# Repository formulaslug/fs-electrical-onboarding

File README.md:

# FS Electrical Onboarding

This git repository contains onboarding projects for each electrical subsystem:

- Low Voltage (LV)
- Power Electronics (PE)
- Firmware (FW)

You must complete one onboarding project to be able to join the team. Our goal
is to get to know you and how you work, not to grade your skills or abilities
coming in. We want to see that you're excited and willing to learn, not that you
know everything already! To make team roster selection easier for us, you'll
only officially be assigned to one specific subsystem within the Electrical
team. But once you've joined, you're encouraged to contribute and participate in
as many ways as you're excited to and have bandwidth for.

**Read the README file in each subsystem's folder in this repo to get started on
the onboarding project for that subsystem.** You are encouraged to attempt
whichever of the three onboarding projects that you find interesting!

---

Note: Clone this repository recursively (`git clone --recursive`). If you
didn't, be sure to initialize the submodule: `git submodule init` _and_ `git
submodule update`

**IMPORTANT:** To start your project, create a branch in this repo with your
first and last name. For example: `jack-nystrom`. Then do your work in that
branch!

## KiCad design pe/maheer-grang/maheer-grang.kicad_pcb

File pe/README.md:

**Formula Slug Power Electronics Onboarding**

Welcome to Formula Slug's Power Eletronics onboarding project! Refer to this
Google Doc for all information regarding this project:

[View the FS Power Electronics Onboarding Guide 26-27](https://docs.google.com/document/d/1htf_bj8dCnWR_2gC1TFTzJU0MFP1d0OxF1IBO_kqalM/edit?usp=sharing)

---

Note: Clone this repository recursively (`git clone --recursive`). If you
didn't, be sure to initialize the submodule: `git submodule init` _and_ `git
submodule update`

**IMPORTANT:** To start your project, create a branch in this repo with your
first and last name. For example: `jack-nystrom`. Then do your work in that
branch!

# Kicad Projects

## Creating a project

1. Install our Template Project to your local computer.
   - Kicad requires templates to be installed locally, but our template is
     stored in the `template` folder in this repo, so you'll need to copy the
     `template` folder to where Kicad expects it. To see where that is, press
     Preferences -> Configure Paths, and look for the value of
     `KICAD_USER_TEMPLATE_DIR`. Copy the `template` folder there.
2. Create a new branch _from main_. Name your branch in-kebab-case
3. Create a new Kicad project from template. Under "User Templates" you should
   now see our Formula Slug template listed! Navigate to `fs-5-schematics` in
   the dialog and name your project the same as your branch name
   (in-kebab-case). This should create a new folder for your project inside of
   `fs-5-schematics`.
5. In the Schematic Editor, open File -> Schematic Setup -> Text Variables, and
   fill in the info for your board.
6. Create an initial commit and get to work!

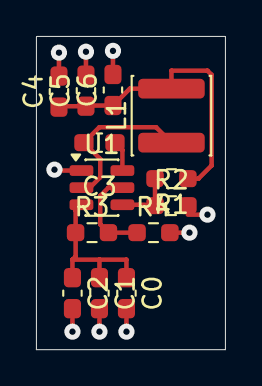
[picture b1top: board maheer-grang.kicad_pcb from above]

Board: 2 copper layers, 10.5 x 17.4 mm, 13 parts (0 on the bottom side), 7 nets.

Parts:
C0, C1, C2: 10 µF; C_0603_1608Metric_Pad1.08x0.95mm_HandSolder
C3: 100 nF; C_0603_1608Metric_Pad1.08x0.95mm_HandSolder
C4, C5, C6: 22 µF; C_0603_1608Metric_Pad1.08x0.95mm_HandSolder
L1: 4.7 µH; L_Pulse_PA4332
R1: 56.2k; R_0603_1608Metric_Pad0.98x0.95mm_HandSolder
R2: 10K; R_0603_1608Metric_Pad0.98x0.95mm_HandSolder
R3: 221K; R_0603_1608Metric_Pad0.98x0.95mm_HandSolder
R4: 32.4K; R_0603_1608Metric_Pad0.98x0.95mm_HandSolder
U1: AP62300TWU; TSOT-23-6

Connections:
GNDREF: C0.2, C1.2, C2.2, C4.2, C5.2, C6.2, R2.2, R4.2, U1.1 (GND)
unnamed: C4.1, C5.1, C6.1, L1.2, R1.1
unnamed: C3.1, U1.6 (BST)
unnamed: R3.2, R4.1, U1.5 (EN)
unnamed: R1.2, R2.1, U1.4 (FB)
unnamed: C0.1, C1.1, C2.1, R3.1, U1.3 (IN)
unnamed: C3.2, L1.1, U1.2 (SW)

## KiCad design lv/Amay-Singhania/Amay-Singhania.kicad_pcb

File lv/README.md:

**Welcome to Formula Slug Low Voltage Onboarding**

In order to get to know you and your passions better, we are asking you to complete
an open ended racecar-related project in one of a few formats. Our goal is not
to evaluate any of your skills, but rather to learn about how you approach difficult
and uncertian things.

For the purposes of whichever LV project you choose to do, **I (Luca) am available to help you!**
(and would appreciate getting to know you better)
I will be in BE-49 (or sometimes Jacks Lounge) at the times published in the electrical leads
office hours calendar, and you can always shoot me a slack message.

# What does LV do?
LV team designs all the PCBs and electrical wiring on the car. There's lots of
interesting safety features which are rules required to be implemented in hardware,
and we also try to pack more and more sensors onto the car each year.

As part of LV, you should expect to face challenges like:
- Design a circuit to detect a high-current output from the battery at the same time
as high brake pressure (see: BSPD)
- Design a circuit to measure small resistance changes of a circuit in a high-noise
enviornment (see: Strain Gauges)
- Select parts (sheathing, wire, crimps) with which to wire the car
- Debug startup transient conditions causing fault lights to flash when the car
is turned on
- Layout components on a PCB to obey mechanical, thermal, and safety constraints
- Source and implement sensors
- Debug communication busses on the car like CAN, analog signals, Serial, an PWM

You can find exmaples of the work LV has done all over the car, as well as in
the [schematics repository](https://github.com/formulaslug/fs-4-schematics). You
can also see some awesome sensor data collected on LV PCBs in our [grafana
dashboard](https://graf.telemetry.formulaslug.com/d/lyffkrd/library-dashboard?orgId=1&from=1970-01-01T00:00:00.011Z&to=1970-01-01T00:04:08.856Z&timezone=utc&var-srcfile=FS-4%2Fttt%2Fcandump-2026-06-11_155420.parquet).

# Project Options
Reminder: These are big bites, we know that most poeple can't produce a car-ready
outcome for any of these... that's okay :). We just want to see how you'll go at
it. Aim to spend less than 5 hours on these, and try to involve as much of your
own thinking as possible. Your personal effort will be noticed. Chose one of these
projects, create a branch of this repository, and create a subfolder of /lv containing
your work/research. You can also propose literally anything else you'd like to do
as an onboarding project.

> [!CAUTION]
> **Don't get overwhelmed. Come talk to me. I want to help you. This is supposed to be hard. You're not supposed to do a good job.**

## Air pressure / temperature / humidity
Our racecar has two main applications for aerometric sensors: monitoring the
cooling of the battery, and validating simulations of the aerodynamic elements
on the car. Do some research to determine what parameters (accuracy, resolution,
range) are needed for these applications and source a sensor (on digikey or mouser).
You can also describe how you'd make your own sensor (or sensor array) for this applciation
(and I'd love to hear it).

One example of such a sensor is the [BMP180](https://www.digikey.com/en/products/detail/bosch-sensortec/BMP180/2688259).
It's a MEMS (micro electro mechanical system) which measures pressure. It has great software
support because lots of Arduino modules use it, but it's no longer manufactured, and has
decent resolution, but since it communicates with I2C and has no address pins (inputs which allow I2C address configuration), it would be
difficult to use several of them together with one microcontroller.

Try to find a sensor which has at least the resolution of the BMP180, but has a communication
or output interface which allows it to be banked with several others on the same PCB. I
recommend reading briefly about common sensor output interfaces (analog, I2C, SPI, oneWire),
so you can understand which are easiest to use with multiple of the same sensor.

Identify some key parameters, and compile your questions/thoughts, and then **check in with me.**

## FPC suspension strain gauge
We order our PCBs from [JLC](https://jlcpcb.com). JLC can also make something called
an [FPC](https://jlcpcb.com/pcb-fabrication/flexible-pcb). Read about how [strain gauges](https://en.wikipedia.org/wiki/Strain_gauge) 
work, do some research about how other FSAE teams have
implemented strain gauges on their suspension members, and attempt to design your own
strain gauge to be manufactured as an FPC. I have not seen other teams do this before, but
it has some benefits and drawbacks... try to find those. 

Once you've put some thought into it and have an idea of how these things work, I want you to
do a teeny bit of math. Use an online calculator, relevant equations and constants, or the
calculator built into Kicad to compute the necessary length of minimum width copper trace ([here are jlc's minimums](https://jlcpcb.com/capabilities/flex-pcb-capabilities))
needed to equal 350 Ohm's of resistance. Take this a step farther, and determine the size of
rectangle needed to fit those traces according to JLC's published minimum trace width and
trace clearance (width between traces).

At this point or if you get stuck, **come check in with me.**

This project will be a PCB, so
instead of creating a blank folder with markdown or text files documenting your research,
create a copy of the kicad template folder (see below). You can still include any research
as text files. This is one project we are very excited about as a team, and which will make
a big impact on DAQ (Data Aquisition).

## Design a BSPD circuit
Every FSAE EV car is required to have a device called the "Brake system plausibility device".
Read about it in EV8.7 of the [2027 rules](https://fsaeonline.com/cdsweb/gen/DownloadDocument.aspx?DocumentID=9574fa97-c13e-4b90-9c75-044e30348cab).
We use the following sensors for this device, but you can choose others for the purpose of this project if you prefer:
- [Brake Pressure](https://www.summitracing.com/parts/aag-s0050?srsltid=AU7gw4WvwmFzL4ESdIDoUFAQyi38mjfxpO6NWv7JNG3hZhB_v7D9QLCm)
- [Current Sensor](https://www.lem.com/sites/default/files/products_datasheets/hass-50_600-s-v22.pdf)
This project will be a schematic, so instead of creating a blank folder with markdown or 
text files documenting your research, create a copy of the kicad template folder 
(see below). You can still include any research as text files.

Hint: You'll need to use Op-Amps to compare and scale voltages.

You do not need to start immediately with Kicad. It can be a bit much. Start by creating a
schematic for an Op-Amp based comparator (google that). Capture it somehow (on paper, in Kicad, whatever).
**Then come and check in with me to talk it through.**

I expect many of you will be overwhelmed trying to figure out how op-amps work. Find some resources (a video, article, etc),
and as you hear terms you do not understand, work your way backwards. You can learn much of the fundamentals of
~2 entire classes if you are intellectually responsible in teaching yourself this way. If you feel like giving up, come
find me.

## In-Helmet Audio
We want to add radio based driver communications to our telemetry system. This project
specifically relates to the speakers and microphone in the drivers (motorcycle) helmet,
and perhaps the driver circuitry to convert a convenient digital signal to and from the
interface to the microphone/speakers. Find speakers and microphone(s) sourceable on
digikey and propose how they can be packaged into the helmet without compromising ergonomics.
Think about how this system can connect to wiring on the car with a connector
that is both robust and breakaway--that is, the driver needs to be able to get out of the car
quickly in an emergency and won't have time to unlatch any extra electrical connections.

[Here's](https://www.digikey.com/en/products/detail/same-sky-formerly-cui-devices/CSS-66668N/6145945) 
an example of the type of speaker driver that would be in a pair of headphones.
This particular one is very large. Determine if a large driver is necessary in this application,
or rather what advantage a larger driver has, and find one which is appropriate. Similarly,
think about the challenges a microphone in this application faces, and try to find one which
is suitable.

As you select components, remember to focus on both their electrical/audio performance,
and their ergonomics/dimensions as they relate to this application. **Find me when you source
at least 2/3 components (microphone, speaker, connector).**

# General Notes

- Clone this repository recursively (`git clone --recursive`). If you didn't, be
  sure to initialize the submodule: `git submodule init` _and_ `git submodule
update`

**IMPORTANT:** To start your project, create a branch in this repo with your
first and last name. For example: `jack-nystrom`. Then do your work in that
branch!

# Kicad Projects

## Creating a project

1. Install our Template Project to your local computer.
   - Kicad requires templates to be installed locally, but our template is
     stored in the `template` folder in this repo, so you'll need to copy the
     `template` folder to where Kicad expects it. To see where that is, press
     Preferences -> Configure Paths, and look for the value of
     `KICAD_USER_TEMPLATE_DIR`. Copy the `template` folder there.
2. Create a new branch _from main_. Name your branch in-kebab-case
3. Create a new Kicad project from template. Under "User Templates" you should
   now see our Formula Slug template listed! Navigate to `fs-5-schematics` in
   the dialog and name your project the same as your branch name
   (in-kebab-case). This should create a new folder for your project inside of
   `fs-5-schematics`.
5. In the Schematic Editor, open File -> Schematic Setup -> Text Variables, and
   fill in the info for your board.
6. Create an initial commit and get to work!

## LV Standards

https://docs.google.com/document/d/1JF8Ld86JzdSsicxHTWAqBsUBFZuK-cVn7AItZKhkslQ/edit?usp=sharing

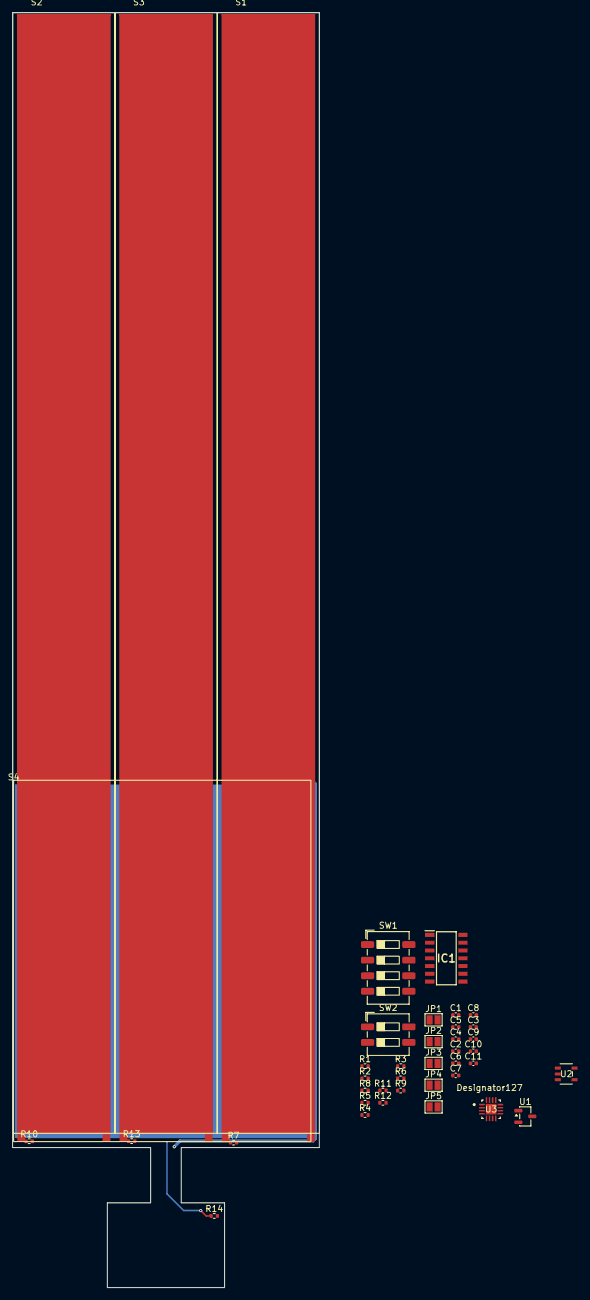
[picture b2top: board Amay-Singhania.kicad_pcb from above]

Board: 2 copper layers, 50.0 x 207.8 mm, 40 parts (0 on the bottom side), 25 nets.

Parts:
C1, C2, C3, C5, C6, C7, C8: 0.1uF; C_0402_1005Metric
C4: 100uF; C_0402_1005Metric
C9, C10, C11: 100nF; C_0402_1005Metric
IC1: TLV4888DR; SOIC127P600X175-14N
JP1, JP2, JP3, JP4, JP5: SolderJumper-2_P1.3mm_Open_Pad1.0x1.5mm
R1, R2, R7, R10, R13, R14: 350; R_0402_1005Metric
R3, R4, R8, R11, R12: 470R; R_0402_1005Metric
R5: 10kR; R_0402_1005Metric
R6, R9: 4.7kR; R_0402_1005Metric
S1, S2, S3: StrainGaugeAxial; Strain Gauge V1
S4: StrainGaugeReference; ReferenceStrainGauge
SW1: SW_DIP_x04; SW_DIP_SPSTx04_Slide_6.7x11.72mm_W6.73mm_P2.54mm_LowProfile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
SW2: SW_DIP_x02; SW_DIP_SPSTx02_Slide_6.7x6.64mm_W6.73mm_P2.54mm_LowProfile_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
U1: SL7550-3; SOT-23-3
U2: LDK320AM33R; SOT23-5L_STM
U3: ADS122C14IRTER; RTE0016C-IPC_A

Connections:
1V65: C3.2, JP5.2, R3.1, U3.8 (AIN7_GPIO3_DRDY_CLKIN_N)
+3V3: C9.1, C10.1, R1.1, R6.1, R9.1, S1.2, S2.2, S3.2, S4.2, SW1.5, SW2.3, U2.5 (OUT), U3.13 (DVDD), U3.15 (AVDD)
+5V: C1.1, IC1.4 (V+), U1.2 (VOUT), U2.1 (IN), U2.3 (EN)
ADC_SCL: R6.2, SW1.7, U3.12 (SCL)
ADC_SDA: R9.2, SW1.8, U3.11 (SDA)
Center_Gauge: C2.2, JP1.1, R4.2, U3.3 (AIN2)
Center_Gauge_Unbuffered: IC1.5 (+IN_B), R7.1, S1.1
GND: C1.2, C2.1, C3.1, C4.1, C5.1, C6.1, C7.1, C8.2, C9.2, C10.2, C11.1, R2.2, R7.2, R10.2, R13.2, R14.2, SW1.6, SW2.4, U1.1 (GND), U2.2 (GND), U3.14 (GND), U3.17 (Thermal_Pad)
Left_Gauge: C7.2, JP3.1, R12.2, U3.1 (AIN0)
Left_Gauge_Unbuffered: IC1.12 (+IN_D), R10.1, S2.1
unnamed: IC1.1 (OUT_A), IC1.2 (-IN_A), R5.2, R8.2
unnamed: IC1.6 (-IN_B), IC1.7 (OUT_B), JP1.2, R4.1
unnamed: IC1.8 (OUT_C), IC1.9 (-IN_C), JP2.2, R11.1
unnamed: IC1.13 (-IN_D), IC1.14 (OUT_D), JP3.2, R12.1
unnamed: C8.1, IC1.11 (V-)
unnamed: R1.2, R2.1, R3.2
unnamed: SW1.1, SW1.2, SW1.3, SW1.4, U3.9 (A0)
unnamed: SW2.1, SW2.2, U3.10 (A1)
unnamed: JP4.2, JP5.1, U3.2 (AIN1), U3.4 (AIN3), U3.6 (AIN5_REFN_GPIO1)
unnamed: C11.2, U3.16 (REFOUT)
Reference_Gauge: C5.2, R8.1, U3.7 (AIN6_GPIO2_FAULT_N)
Reference_Gauge_Filtered: C4.2, JP4.1, R5.1
Reference_Gauge_Unbuffered: IC1.3 (+IN_A), R14.1, S4.1
Right_Gauge: C6.2, JP2.1, R11.2, U3.5 (AIN4_REFP_GPIO0)
Right_Gauge_Unbuffered: IC1.10 (+IN_C), R13.1, S3.1

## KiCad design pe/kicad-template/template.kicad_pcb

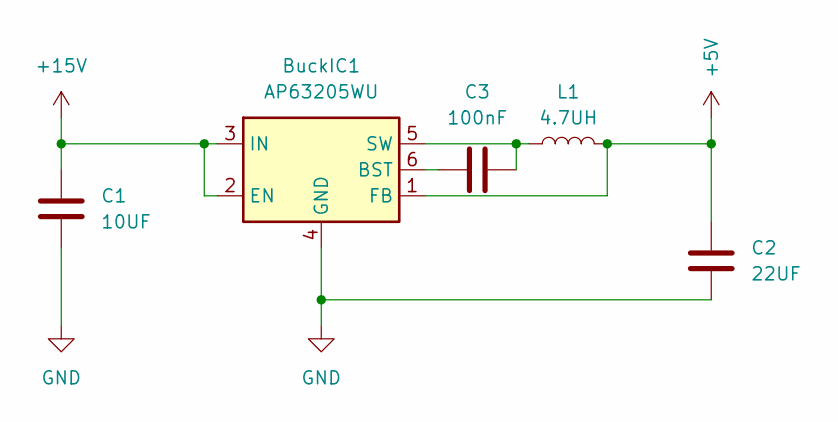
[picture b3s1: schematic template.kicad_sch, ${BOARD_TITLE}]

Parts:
BuckIC1: AP63205WU; TSOT-23-6; MFG PN AP63205WU-7; DIGI PN AP63205WU-7DITR-ND
C1: 10UF; C_0603_1608Metric; MFG PN CC0603MRX5R8BB106; Digi PN 311-3494-2-ND
C2: 22UF; C_0603_1608Metric; MFG PN C1608X5R1A226M080DC; DIGI PN 445-C1608X5R1A226M080DCTR-ND
C3: 100nF; C_0603_1608Metric; MFG PN C0603C104K5RACTU; DIGI PN 399-C0603C104K5RACTUTR-ND
L1: 4.7UH; L_Bourns_SRP5030T; MFG PN SRP5030TA-4R7M; DIGI PN SRP5030TA-4R7MTR-ND

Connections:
+5V: BuckIC1.1 (FB), C2.1, L1.2
+15V: BuckIC1.2 (EN), BuckIC1.3 (IN), C1.1
GND: BuckIC1.4 (GND), C1.2, C2.2
unnamed: BuckIC1.6 (BST), C3.1
unnamed: BuckIC1.5 (SW), C3.2, L1.1

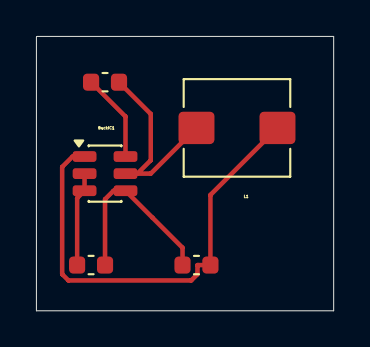
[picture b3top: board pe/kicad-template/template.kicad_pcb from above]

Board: 2 copper layers, 16.5 x 15.2 mm, 5 parts (0 on the bottom side), 5 nets.

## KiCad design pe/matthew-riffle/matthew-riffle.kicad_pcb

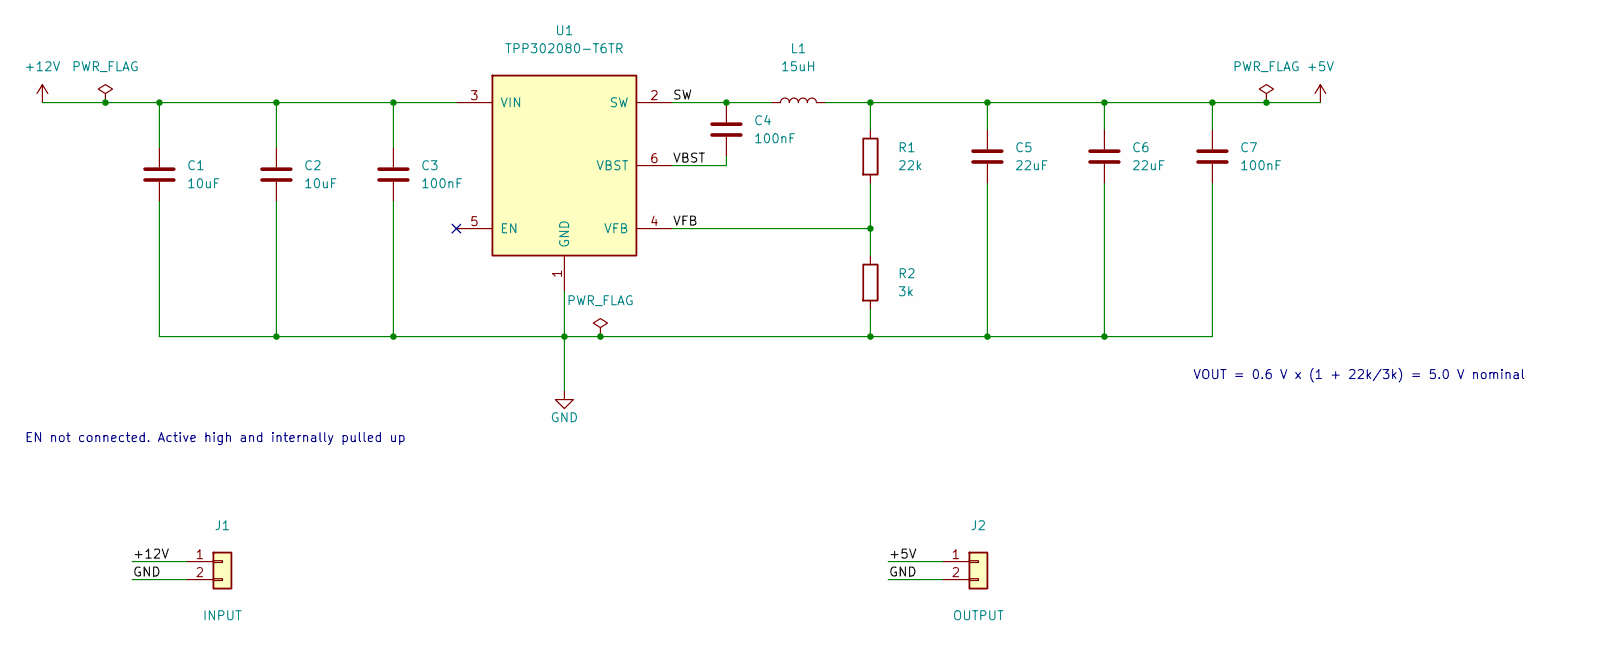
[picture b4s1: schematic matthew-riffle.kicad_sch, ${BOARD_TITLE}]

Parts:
C1, C2: 10uF; C_0603_1608Metric_Pad1.08x0.95mm_HandSolder; Rating 25V, X5R; Manufacturer Part Number GRM188R61E106MA73J; Digikey Part Number 490-12737-1-ND
C3, C4, C7: 100nF; C_0603_1608Metric_Pad1.08x0.95mm_HandSolder; Rating 25V, X7R; Manufacturer Part Number CGA3E2X7R1E104K080DA; Digikey Part Number 445-CGA3E2X7R1E104K080DACT-ND
C5, C6: 22uF; C_0603_1608Metric_Pad1.08x0.95mm_HandSolder; Rating 10V, X5R; Manufacturer Part Number GRM187R61A226ME15D; Digikey Part Number 490-13243-1-ND
J1: INPUT; SolderWire-0.75sqmm_1x02_P4.8mm_D1.25mm_OD2.3mm
J2: OUTPUT; SolderWire-0.75sqmm_1x02_P4.8mm_D1.25mm_OD2.3mm
L1: 15uH; L_Eaton_HCM1A0805V3_1R0_to_330; Manufacturer Part Number HCM1A0805V3-150-R; Digikey Part Number 283-HCM1A0805V3-150-RCT-ND
R1: 22k; R_0603_1608Metric_Pad0.98x0.95mm_HandSolder; Manufacturer Part Number RG1608P-223-B-T5; Digikey Part Number RG16P22.0KBCT-ND
R2: 3k; R_0603_1608Metric_Pad0.98x0.95mm_HandSolder; Manufacturer Part Number RG1608P-302-B-T5; Digikey Part Number RG16P3.0KBCT-ND
U1: TPP302080-T6TR; TSOT-23-6_HandSoldering; Manufacturer Part Number TPP302080-T6TR; Digikey Part Number 5503-TPP302080-T6TRCT-ND

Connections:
+5V: C5.1, C6.1, C7.1, J2.1, L1.2, R1.1
+12V: C1.1, C2.1, C3.1, J1.1, U1.3 (VIN)
/SW: C4.1, L1.1, U1.2 (SW)
/VBST: C4.2, U1.6 (VBST)
/VFB: R1.2, R2.1, U1.4 (VFB)
GND: C1.2, C2.2, C3.2, C5.2, C6.2, C7.2, J1.2, J2.2, R2.2, U1.1 (GND)

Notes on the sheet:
VOUT = 0.6 V x (1 + 22k/3k) = 5.0 V nominal
EN not connected. Active high and internally pulled up

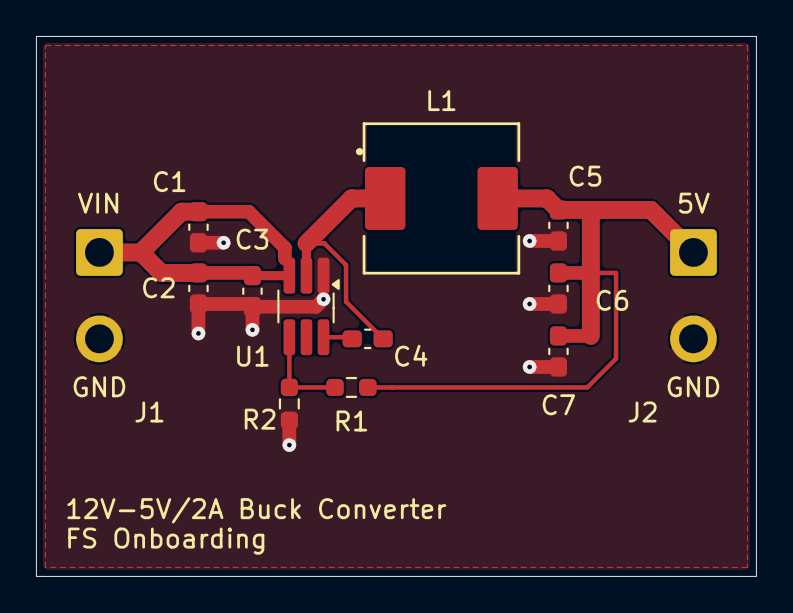
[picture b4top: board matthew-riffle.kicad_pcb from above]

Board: 2 copper layers, 40.0 x 30.0 mm, 13 parts (0 on the bottom side), 6 nets.

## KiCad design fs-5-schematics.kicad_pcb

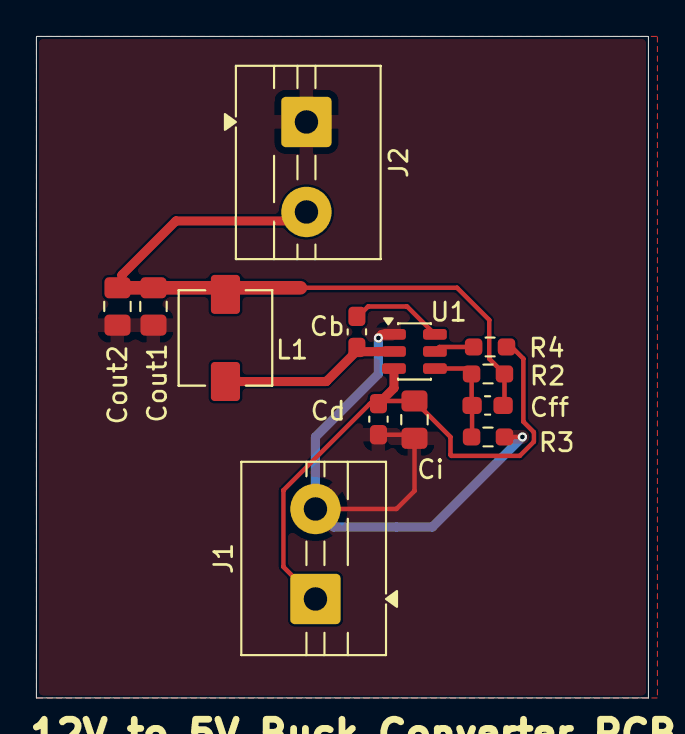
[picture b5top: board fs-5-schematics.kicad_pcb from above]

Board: 2 copper layers, 34.0 x 36.8 mm, 13 parts (0 on the bottom side), 7 nets.

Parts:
Cb: 0.1uF; C_0603_1608Metric_Pad1.08x0.95mm_HandSolder
Cd: 0.1uF; C_0603_1608Metric_Pad1.08x0.95mm_HandSolder
Cfeedfoward1: 75pF; C_0603_1608Metric_Pad1.08x0.95mm_HandSolder
Ci: 10uF; C_0805_2012Metric_Pad1.18x1.45mm_HandSolder
Cout1, Cout2: 22uF; C_0805_2012Metric_Pad1.18x1.45mm_HandSolder
J1: 12V; TerminalBlock_MaiXu_MX126-5.0-02P_1x02_P5.00mm
J2: 5V; TerminalBlock_MaiXu_MX126-5.0-02P_1x02_P5.00mm
L1: INDM5752X300N
R2: 100K; R_0603_1608Metric_Pad0.98x0.95mm_HandSolder
R3: 13.5K; R_0603_1608Metric_Pad0.98x0.95mm_HandSolder
R4: 510k; R_0603_1608Metric_Pad0.98x0.95mm_HandSolder
U1: TPS54202DDC; SOT-23-6

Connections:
+5V: Cfeedfoward1.1, Cout1.1, Cout2.1, J2.2, L1.1, R2.1
+12V: Cd.1, Ci.1, J1.1, R4.1, U1.3 (VIN)
GND: Cd.2, Ci.2, Cout1.2, Cout2.2, J1.2, J2.1, R3.2, U1.1 (GND)
unnamed: Cb.1, U1.6 (BOOT)
unnamed: R4.2, U1.5 (EN)
unnamed: Cfeedfoward1.2, R2.2, R3.1, U1.4 (FB)
unnamed: Cb.2, L1.2, U1.2 (SW)

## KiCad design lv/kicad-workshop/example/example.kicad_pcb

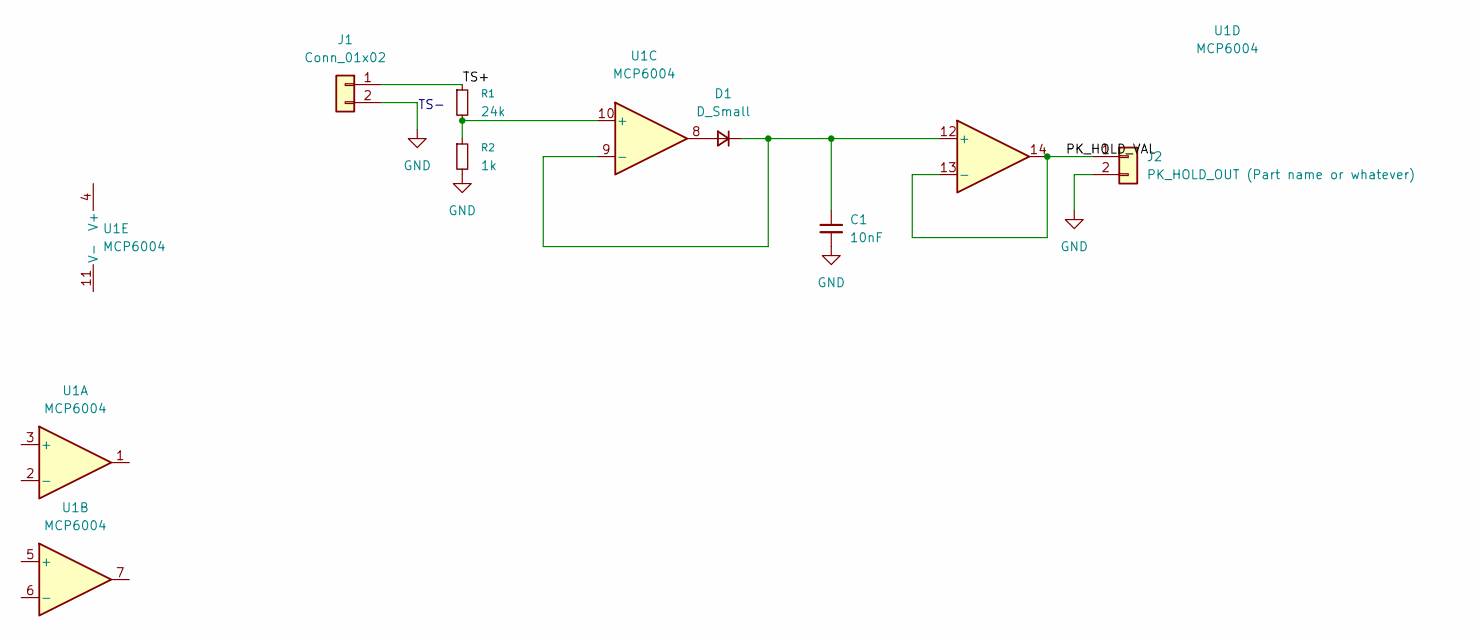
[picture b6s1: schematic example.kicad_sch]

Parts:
C1: 10nF; SOIC-8_3.9x4.9mm_P1.27mm
D1: D_Small; D_0201_0603Metric_Pad0.64x0.40mm_HandSolder
J1: Conn_01x02; PinHeader_1x03_P2.00mm_Vertical_SMD_Pin1Left
J2: PK_HOLD_OUT (Part name or whatever); PinHeader_1x03_P2.00mm_Vertical_SMD_Pin1Left
R1: 24k; R_0603_1608Metric_Pad0.98x0.95mm_HandSolder
R2: 1k; R_0603_1608Metric_Pad0.98x0.95mm_HandSolder
U1: MCP6004; SOIC-14_3.9x8.7mm_P1.27mm

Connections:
/PK_HOLD_VAL: J2.1, U1.13 (-), U1.14
/TS+: J1.1, R1.1
GND: C1.2, J1.2, J2.2, R2.2
unnamed: D1.2 (A), U1.8
unnamed: C1.1, D1.1 (K), U1.9 (-), U1.12 (+)
unnamed: R1.2, R2.1, U1.10 (+)

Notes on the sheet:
TS-

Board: 2 copper layers, 7 parts (0 on the bottom side), 6 nets, no tracks yet.

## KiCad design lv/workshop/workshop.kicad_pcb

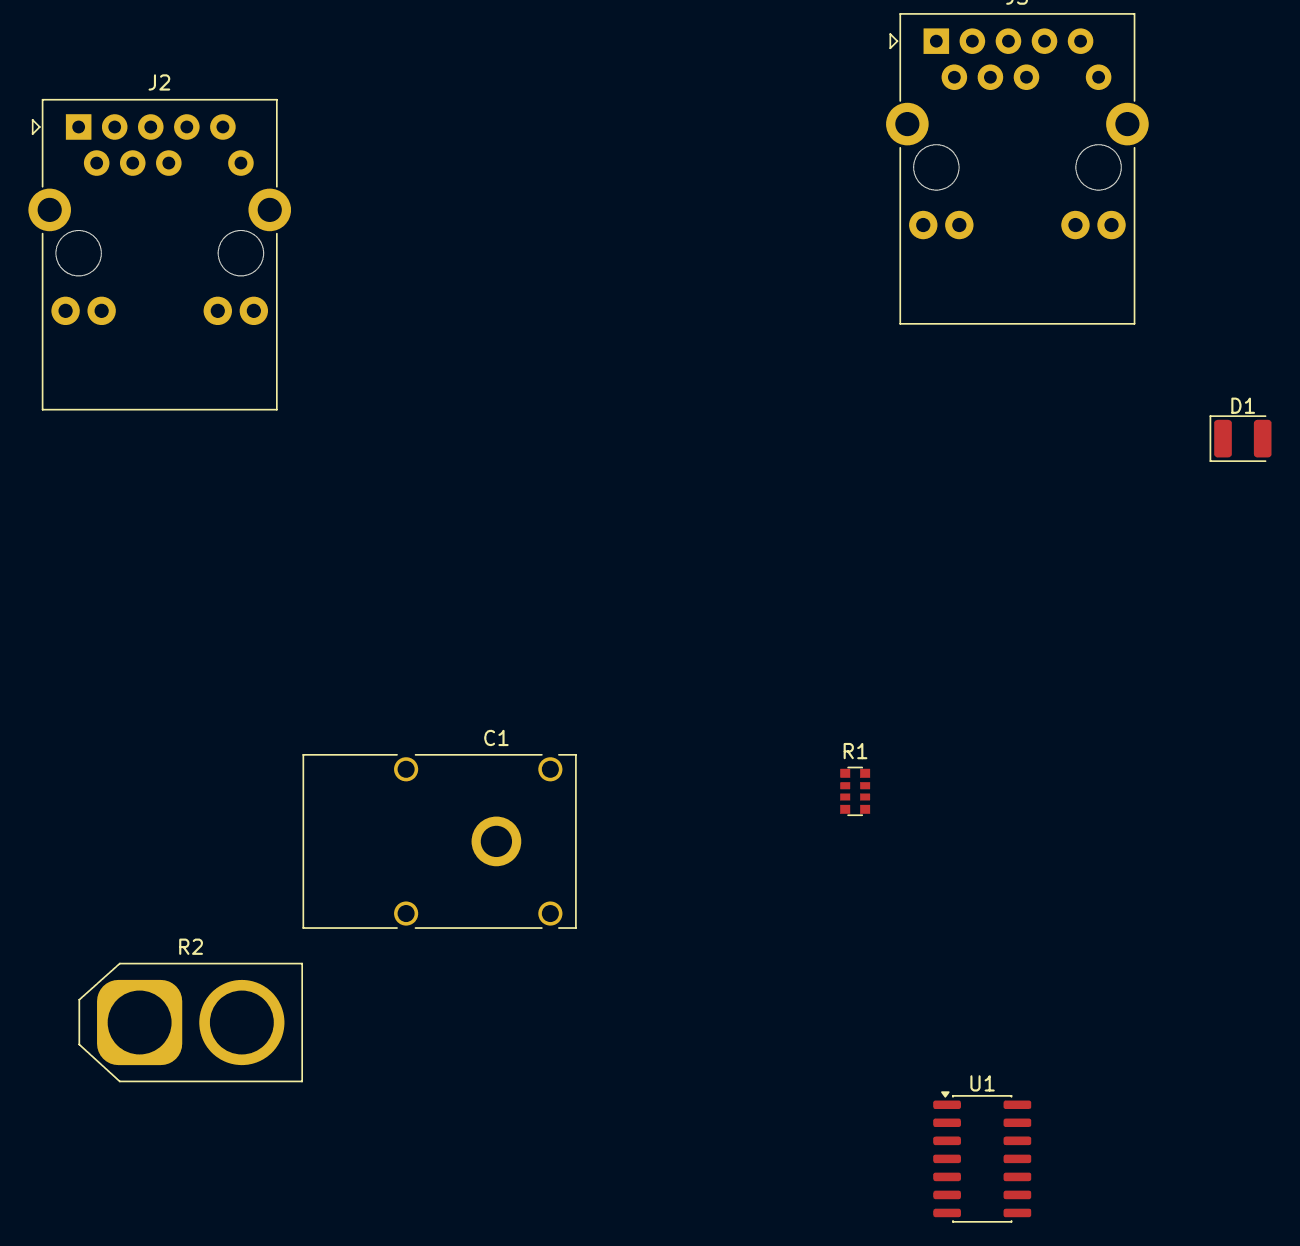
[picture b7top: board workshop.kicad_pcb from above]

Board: 2 copper layers, 7 parts (0 on the bottom side), 6 nets, no tracks yet.

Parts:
C1: C_Small; Banana_Cliff_FCR7350N_S16N-PC_Horizontal
D1: D; D_1210_3225Metric
J2, J3: Conn_01x02; RJ45_Abracon_ARJP11A-MA_Horizontal
R1: 24k; R_Array_Convex_4x0612
R2: 1k; AMASS_XT60-M_1x02_P7.20mm_Vertical
U1: MCP6004; SOIC-14_3.9x8.7mm_P1.27mm

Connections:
GND: J2.1, J3.1, R2.2
unnamed: D1.2 (A), U1.1
unnamed: C1.1, D1.1 (K), U1.2 (-), U1.5 (+)
unnamed: J2.2, R1.1
unnamed: J3.2, U1.6 (-), U1.7
unnamed: R1.2, R2.1, U1.3 (+)

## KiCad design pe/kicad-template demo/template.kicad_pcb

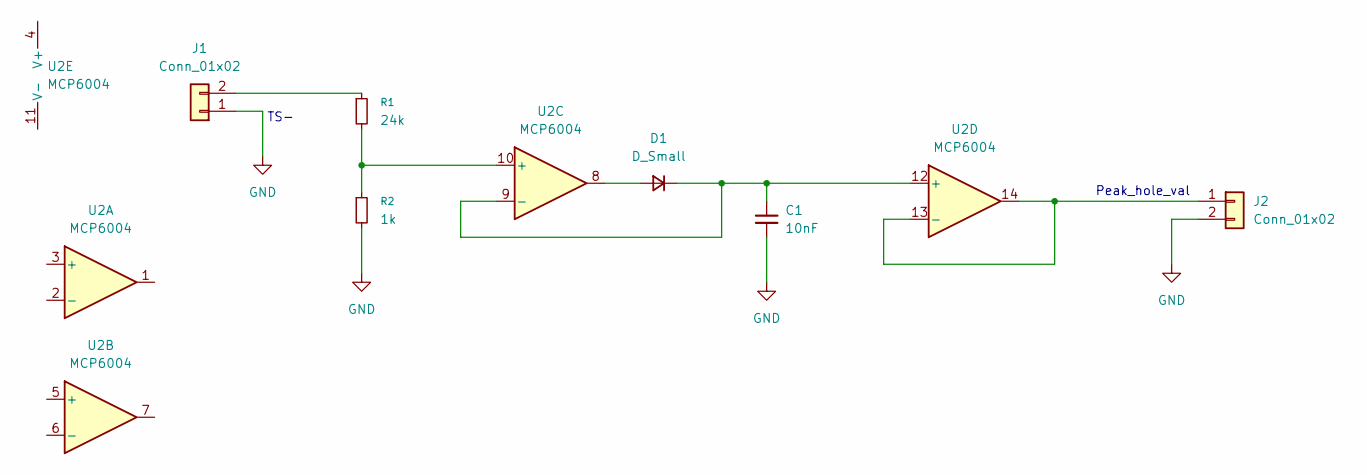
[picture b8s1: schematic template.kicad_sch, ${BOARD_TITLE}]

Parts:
C1: 10nF; C_0201_0603Metric
D1: D_Small; D_0201_0603Metric
J1, J2: Conn_01x02; Banana_Jack_2Pin
R1: 24k; R_4020_10251Metric
R2: 1k; R_4020_10251Metric
U2: MCP6004; SOIC-14_3.9x8.7mm_P1.27mm

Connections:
GND: C1.2, J1.1, J2.2, R2.2
unnamed: D1.2 (A), U2.8
unnamed: C1.1, D1.1 (K), U2.9 (-), U2.12 (+)
unnamed: J1.2, R1.1
unnamed: J2.1, U2.13 (-), U2.14
unnamed: R1.2, R2.1, U2.10 (+)

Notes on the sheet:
TS-
Peak_hole_val

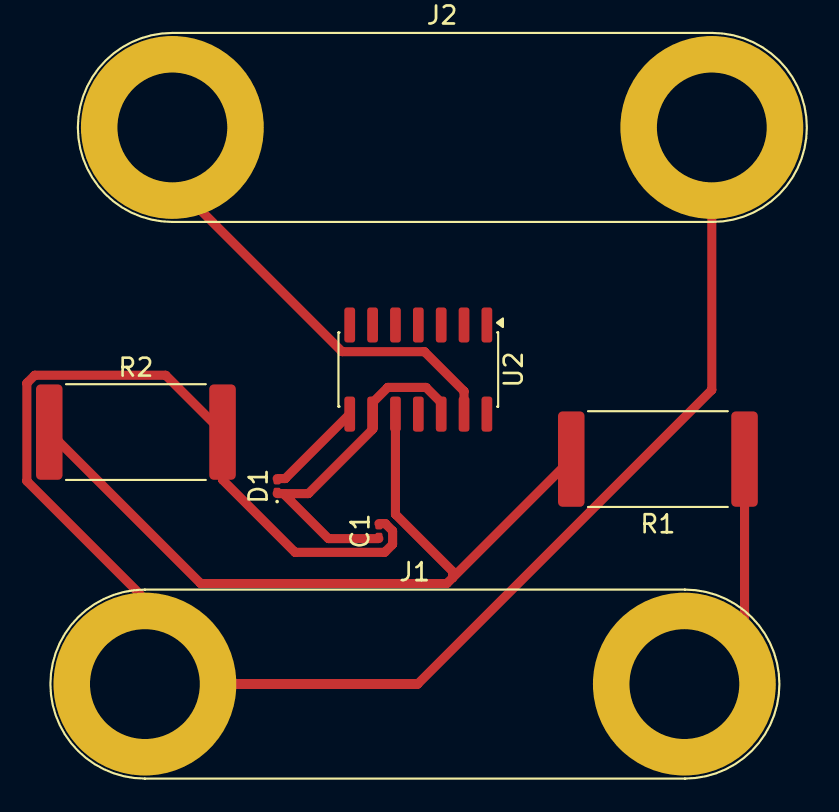
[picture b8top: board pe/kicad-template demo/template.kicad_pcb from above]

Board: 2 copper layers, 7 parts (0 on the bottom side), 6 nets.
